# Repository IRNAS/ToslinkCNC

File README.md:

# ToslinkCNC

CNC machine is usually controlled via parallel bus, containing six signals. For each of the three axes there are two signals: STEP and DIR. At each positive edge of the STEP signal, the corresponding stepper motor moves into direction set by DIR signal. In addition to these six signals, there can also be other general purpose control signals.

Parallel bus on longer distances and in noisy environment can be susceptible to electromagnetic interferences. Because of this we decided to design an interface to transport these parallel signals via an optical link. For successful transfer via optical fiber the first thing that must be done is to convert parallel data to serial bit stream. Moreover, because of the inherent design of optical transmitters and receivers, serial data must also be Manchester encoded.

Our design is based on [Serializer / Deserializer for Audio Fiber Optic](http://opencores.org/project,parallel_io_through_fiber) project published on Open Cores. 

## Use cases
ToslinkCNC has been developed for use with [GoodenoughCNC Plasma](http://goodenoughcnc.eu) cutter as our answer to continuous problems with electrical noise and interference. The following configuration is used in the system. 

## Toslink Receiver-transceiver

For each motor on the CNC machine there is one PCB, containing Toslink receiver. Receiver PCB, together with motor driver, can be mounted on the motor. Receiver is being used with [PoLabs' PoStep25-32 stepper motor driver](http://www.poscope.com/PoStep25-32). PCB is being powered through motor driver connector using +5V. To enable this the +5V supply from motor driver should be connected to unused 9th pin on the driver's IDC connector usign a piece of insulated wire. PCB consists of one CPLD, two optical transmitters, one optical receiver, one DIP switch for selecting the axis and one limit switch / trigger connector. Limit switch is insulated through an optocoupler and trigger output is open drain type. Toslink transmitter DLT1111 and Toslink receiver DLR1111 were used, which enable data transfer speed up to 16 Mbps. We used Xilinx XC9572XL CPLD to implement the necessary logic for protocol conversion. Receivers can also be connected in daisy chain.

### Using IDC-10 connector:

### Using terminal blocks:

## Toslink Transmitter

Transmitter consists of two PCBs, an Arduino sield and a Toslink transciever. Both PCBs are stacked together. Toslink transciever PCB is identical to one used for receiver. Arduino shield consists of headers for Arduino and connectors for [CNC USB Controller Mk3/4 from Planet CNC](http://www.planet-cnc.com/index.php?page=hardware) and PoStep25-32 driver. There is also a terminal block for connecting limit switches and trigger signals. Circuit can be powered either through terminal block (+5V), through Arduino Uno if attached as a shield, or from Planet CNC Controller.

## Toslink Transmitter / Arduino Shield

## Toslink Transmitter / Planet CNC

## Toslink Transmitter / Raspberry Pi Shield

## Firmware Description

All data is being transmitted in frames of fixed length. Frames are transmitted without gaps between them. Each frame contains 3 direction values, 3 step values, vaule of enable signal, 3 values of limit/end switch signals (these fields are being shared with 3 trigger values), parity bits and frame delimiter. To detect parity bit corruption, both even and odd parity bits are being transmitted. Transmitter places direction, step, enable and trigger values in new frame, adds calculated parity bits and sends the frame to the first receiver in daisy chain. Receiver reads the enable value and direction, step and trigger values ( based on axis selection). Receiver replaces the correspondig trigger value with limit switch value, calculates new parity bits and sends this new frame to the next receiver in dasy chain. Output of the last receiver in dasy chain is connected to transmitter input. Transmitter reads all three limit switch values from received frame.

Data in optical fiber is manchester encoded. For logic '0', logic '1' and frame delimiter three different patterns are being used. They were selected so that all of them have the same length and are completely different from each other. Decoding is based on time elapsed between two rising edges of clock. If elapsed time is shorter than 12 clock cycles, receiver decodes it as a short step. If it's longer than 12 and shorter than 20 clock cycles, then it's decoded as a medium step. If elapsed time is longer than 20 clock cycles, it's decoded as a long step.

Main transmitter module consists of a step sampler and an optical transmitter. Step sampler samples and shapes incomming step, direction, enable and trigger signals and passes them forward to the optical transmitter. Optical transmitter handles data framing, manchester encoding and sends encoded data to Toslink transmitter.

Block diagram of step sampler is presented in figure below:

Optical transmitter consists of shift register and manchester encoder. Shift register block diagram is presented in figure below:

Manchester encoder consists of three look-up tables and one multiplexer. If value of *tx_output* is "00" the '0' pattern, if  "01" the '1' pattern and if "10" the DEL pattern is generated on the output.

Main receiver module consists of an optical receiver and a step generator. Optical receiver accepts signal from Toslink receiver, decodes it and passes extracted data to step generator. It also adds limit signal values, calculates new parity, manchester encodes data and passes it foward to both Tolsink transmitters. Step generator correctly shapes the received signals.

Optical receiver consists of manchester decoder, shift register and manchester encoder (which is identical to the one used in transmitter). Block diagram of receiver shift register is presented in figure below:

Manchester decoder consists of a simple low-pass filter and a step sampler.

Step sampler is a finite state machine. It's diagram of possible states is presented in figure below. Movement between states is based on received step width: short, medium or long. If step width is too long, the connection is lost and motor driver is disabled (enable signal equals to '1'). As soon as the correct manchester symbol is received, the connection is again established.

## Known Isues

 * There is not enough room on the CPLD to hold both, the transmitter and the receiver. To enable transfer of limit switch signals from receivers back to transmitter, there would also need to be an additional optical receiver implemented on the transmitter PCB's CPLD. This problem can be solved by stacking two transcievers one over another. Firmware for the second transciever is available in [Transmitter](Transmitter/return path receiver CPLD VHDL code) folder.

---

#### License

All our projects are as usefully open-source as possible.

Hardware including documentation is licensed under [CERN OHL v.1.2. license](http://www.ohwr.org/licenses/cern-ohl/v1.2)

Firmware and software originating from the project is licensed under [GNU GENERAL PUBLIC LICENSE v3](http://www.gnu.org/licenses/gpl-3.0.en.html).

Open data generated by our projects is licensed under [CC0](https://creativecommons.org/publicdomain/zero/1.0/legalcode).

All our websites and additional documentation are licensed under [Creative Commons Attribution-ShareAlike 4 .0 Unported License] (https://creativecommons.org/licenses/by-sa/4.0/legalcode).

What this means is that you can use hardware, firmware, software and documentation without paying a royalty and knowing that you'll be able to use your version forever. You are also free to make changes but if you share these changes then you have to do so on the same conditions that you enjoy.

Koruza, GoodEnoughCNC and IRNAS are all names and marks of Institut IRNAS Rače. 
You may use these names and terms only to attribute the appropriate entity as required by the Open Licences referred to above. You may not use them in any other way and in particular you may not use them to imply endorsement or authorization of any hardware that you design, make or sell.

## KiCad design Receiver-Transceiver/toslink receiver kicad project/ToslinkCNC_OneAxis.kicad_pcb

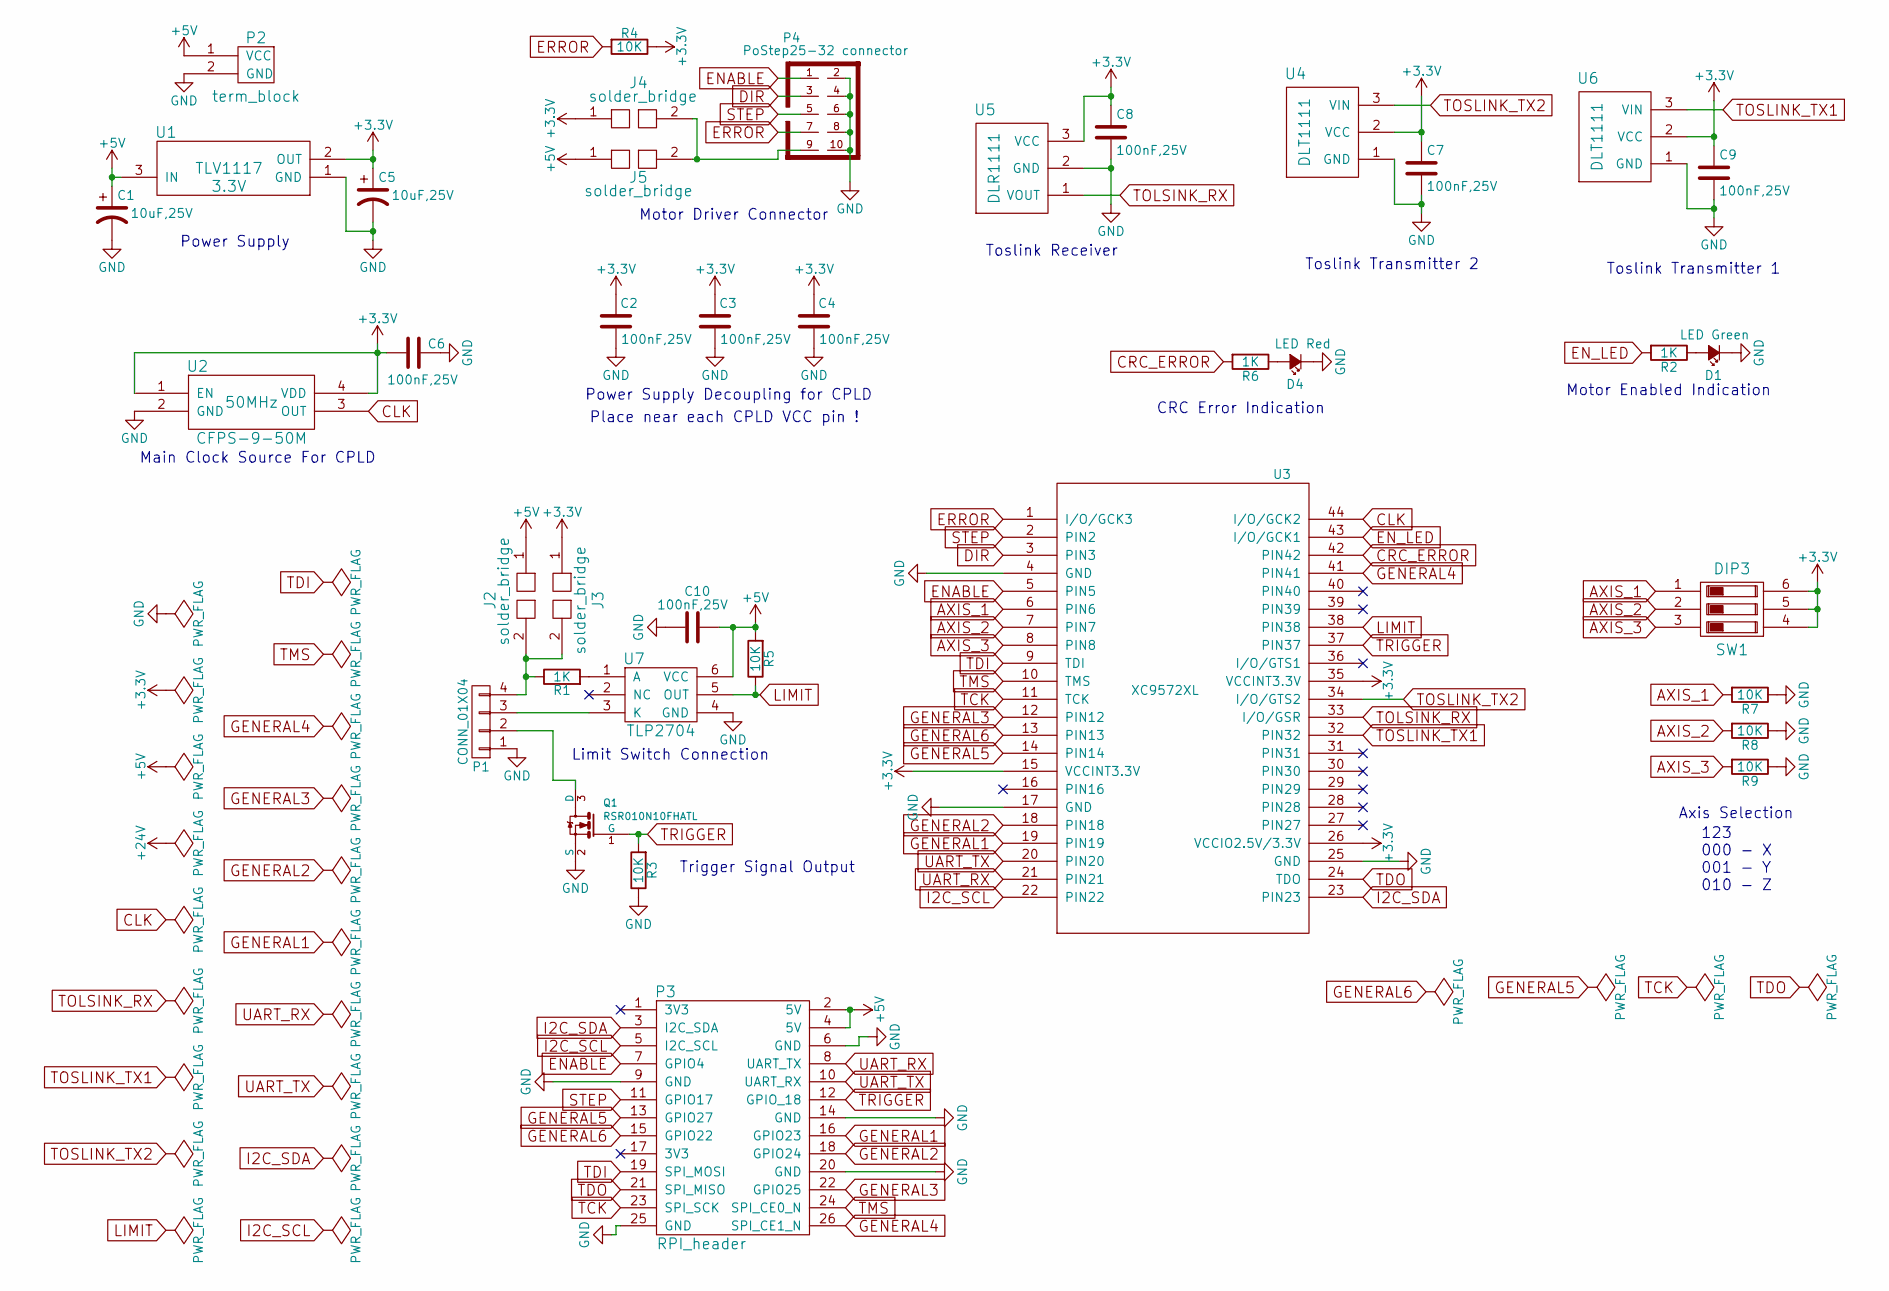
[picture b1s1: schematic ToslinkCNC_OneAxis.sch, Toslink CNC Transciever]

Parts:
C1, C5: 10uF,25V; TantalC_SizeB_EIA-3528_HandSoldering
C2, C3, C4, C6, C7, C8, C9, C10: 100nF,25V; C_0603_HandSoldering
D1: LED Green; LED_0603_HandSoldering
D4: LED Red; LED_0603_HandSoldering
J2, J3, J4, J5: solder_bridge
P1: CONN_01X04; terminal_block_2_5mm_4pole
P2: term_block; terminal_block_2_5mm
P3: RPI_header; Pin_Header_Straight_2x13
P4: PoStep25-32 connector; VASCH5x2
Q1: RSR010N10FHATL; SOT-23
R1, R2, R6: 1K; R_0603_HandSoldering
R3, R4, R5, R7, R8, R9: 10K; R_0603_HandSoldering
SW1: DIP3; OMRON_ELECTRONIC_COMPONENTS_A6S-3102-H_DIP_Switch
U1: TLV1117; SOT-223
U2: CFPS-9-50M
U3: XC9572XL; VQFP44
U4, U6: DLT1111
U5: DLR1111
U7: TLP2704

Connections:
+3V3: C2.2, C3.2, C4.2, C5.1, C6.2, C7.1, C8.1, C9.1, J3.1, J4.1, R4.1, SW1.4, SW1.5, SW1.6, U1.2 (OUT), U2.1 (EN), U2.4 (VDD), U3.15 (VCCINT3.3V), U3.26 (VCCIO2.5V/3.3V), U3.35 (VCCINT3.3V), U4.2 (VCC), U5.3 (VCC), U6.2 (VCC)
+5V: C1.1, C10.1, J2.1, J5.1, P2.1 (VCC), P3.2 (5V), P3.4 (5V), R5.2, U1.3 (IN), U7.6 (VCC)
AXIS_1: R7.2, SW1.1, U3.6 (PIN6)
AXIS_2: R8.2, SW1.2, U3.7 (PIN7)
AXIS_3: R9.2, SW1.3, U3.8 (PIN8)
CLK: U2.3 (OUT), U3.44 (I/O/GCK2)
CRC_ERROR: R6.2, U3.42 (PIN42)
DIR: P4.3, U3.3 (PIN3)
ENABLE: P3.7 (GPIO4), P4.1, U3.5 (PIN5)
EN_LED: R2.2, U3.43 (I/O/GCK1)
ERROR: P4.7, R4.2, U3.1 (I/O/GCK3)
GENERAL1: P3.16 (GPIO23), U3.19 (PIN19)
GENERAL2: P3.18 (GPIO24), U3.18 (PIN18)
GENERAL3: P3.22 (GPIO25), U3.12 (PIN12)
GENERAL4: P3.26 (SPI_CE1_N), U3.41 (PIN41)
GENERAL5: P3.13 (GPIO27), U3.14 (PIN14)
GENERAL6: P3.15 (GPIO22), U3.13 (PIN13)
GND: C1.2, C2.1, C3.1, C4.1, C5.2, C6.1, C7.2, C8.2, C9.2, C10.2, D1.1 (K), D4.1 (K), P1.1, P2.2 (GND), P3.6 (GND), P3.9 (GND), P3.14 (GND), P3.20 (GND), P3.25 (GND), P4.2, P4.4, P4.6, P4.8, P4.10, Q1.2 (S), R3.1, R7.1, R8.1, R9.1, U1.1 (GND), U2.2 (GND), U3.4 (GND), U3.17 (GND), U3.25 (GND), U4.1 (GND), U5.2 (GND), U6.1 (GND), U7.4 (GND)
I2C_SCL: P3.5 (I2C_SCL), U3.22 (PIN22)
I2C_SDA: P3.3 (I2C_SDA), U3.23 (PIN23)
LIMIT: R5.1, U3.38 (PIN38), U7.5 (OUT)
unnamed: D1.2 (A), R2.1
unnamed: D4.2 (A), R6.1
unnamed: J2.2, J3.2, P1.4, R1.1
unnamed: J4.2, J5.2, P4.9
unnamed: P1.2, Q1.3 (D)
unnamed: P1.3, U7.3 (K)
unnamed: R1.2, U7.1 (A)
STEP: P3.11 (GPIO17), P4.5, U3.2 (PIN2)
TCK: P3.23 (SPI_SCK), U3.11 (TCK)
TDI: P3.19 (SPI_MOSI), U3.9 (TDI)
TDO: P3.21 (SPI_MISO), U3.24 (TDO)
TMS: P3.24 (SPI_CE0_N), U3.10 (TMS)
TOLSINK_RX: U3.33 (I/O/GSR), U5.1 (VOUT)
TOSLINK_TX1: U3.32 (PIN32), U6.3 (VIN)
TOSLINK_TX2: U3.34 (I/O/GTS2), U4.3 (VIN)
TRIGGER: P3.12 (GPIO_18), Q1.1 (G), R3.2, U3.37 (PIN37)
UART_RX: P3.8 (UART_TX), U3.21 (PIN21)
UART_TX: P3.10 (UART_RX), U3.20 (PIN20)

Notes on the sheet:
Power Supply Decoupling for CPLD
Axis Selection
Motor Enabled Indication
CRC Error Indication
Place near each CPLD VCC pin !
Main Clock Source For CPLD
Motor Driver Connector
Toslink Transmitter 2
Toslink Receiver
Toslink Transmitter 1
Limit Switch Connection
Power Supply
123 000 - X 001 - Y 010 - Z
Trigger Signal Output

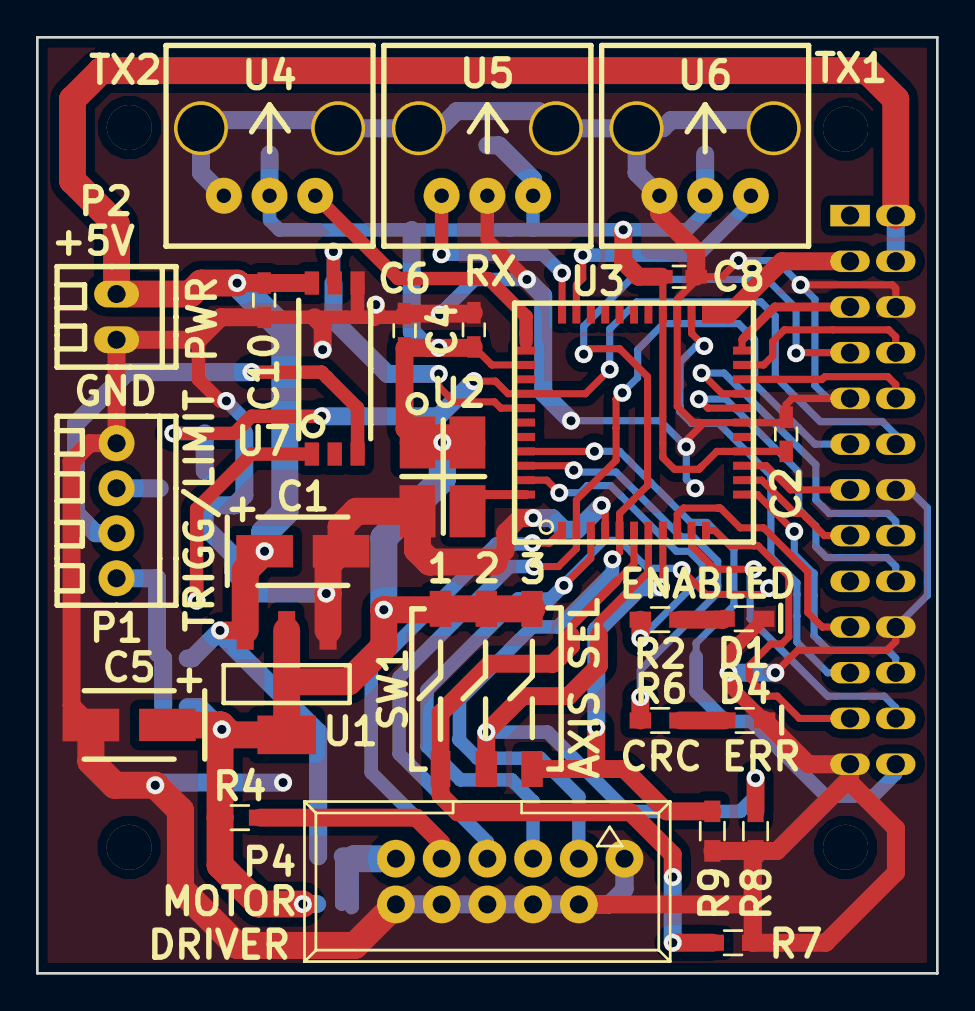
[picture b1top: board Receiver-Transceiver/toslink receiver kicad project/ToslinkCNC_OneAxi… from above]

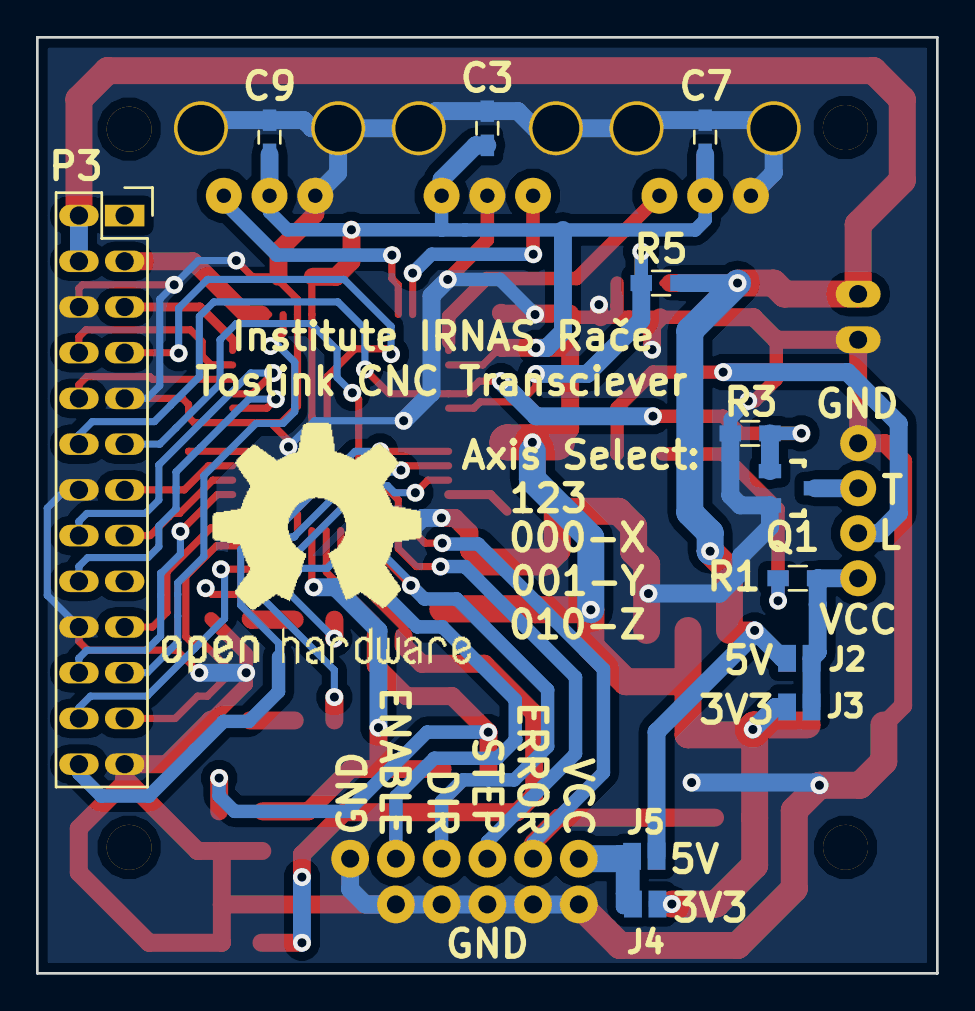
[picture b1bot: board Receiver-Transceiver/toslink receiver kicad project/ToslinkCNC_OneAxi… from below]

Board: 2 copper layers, 50.0 x 52.0 mm, 38 parts (11 on the bottom side), 39 nets.

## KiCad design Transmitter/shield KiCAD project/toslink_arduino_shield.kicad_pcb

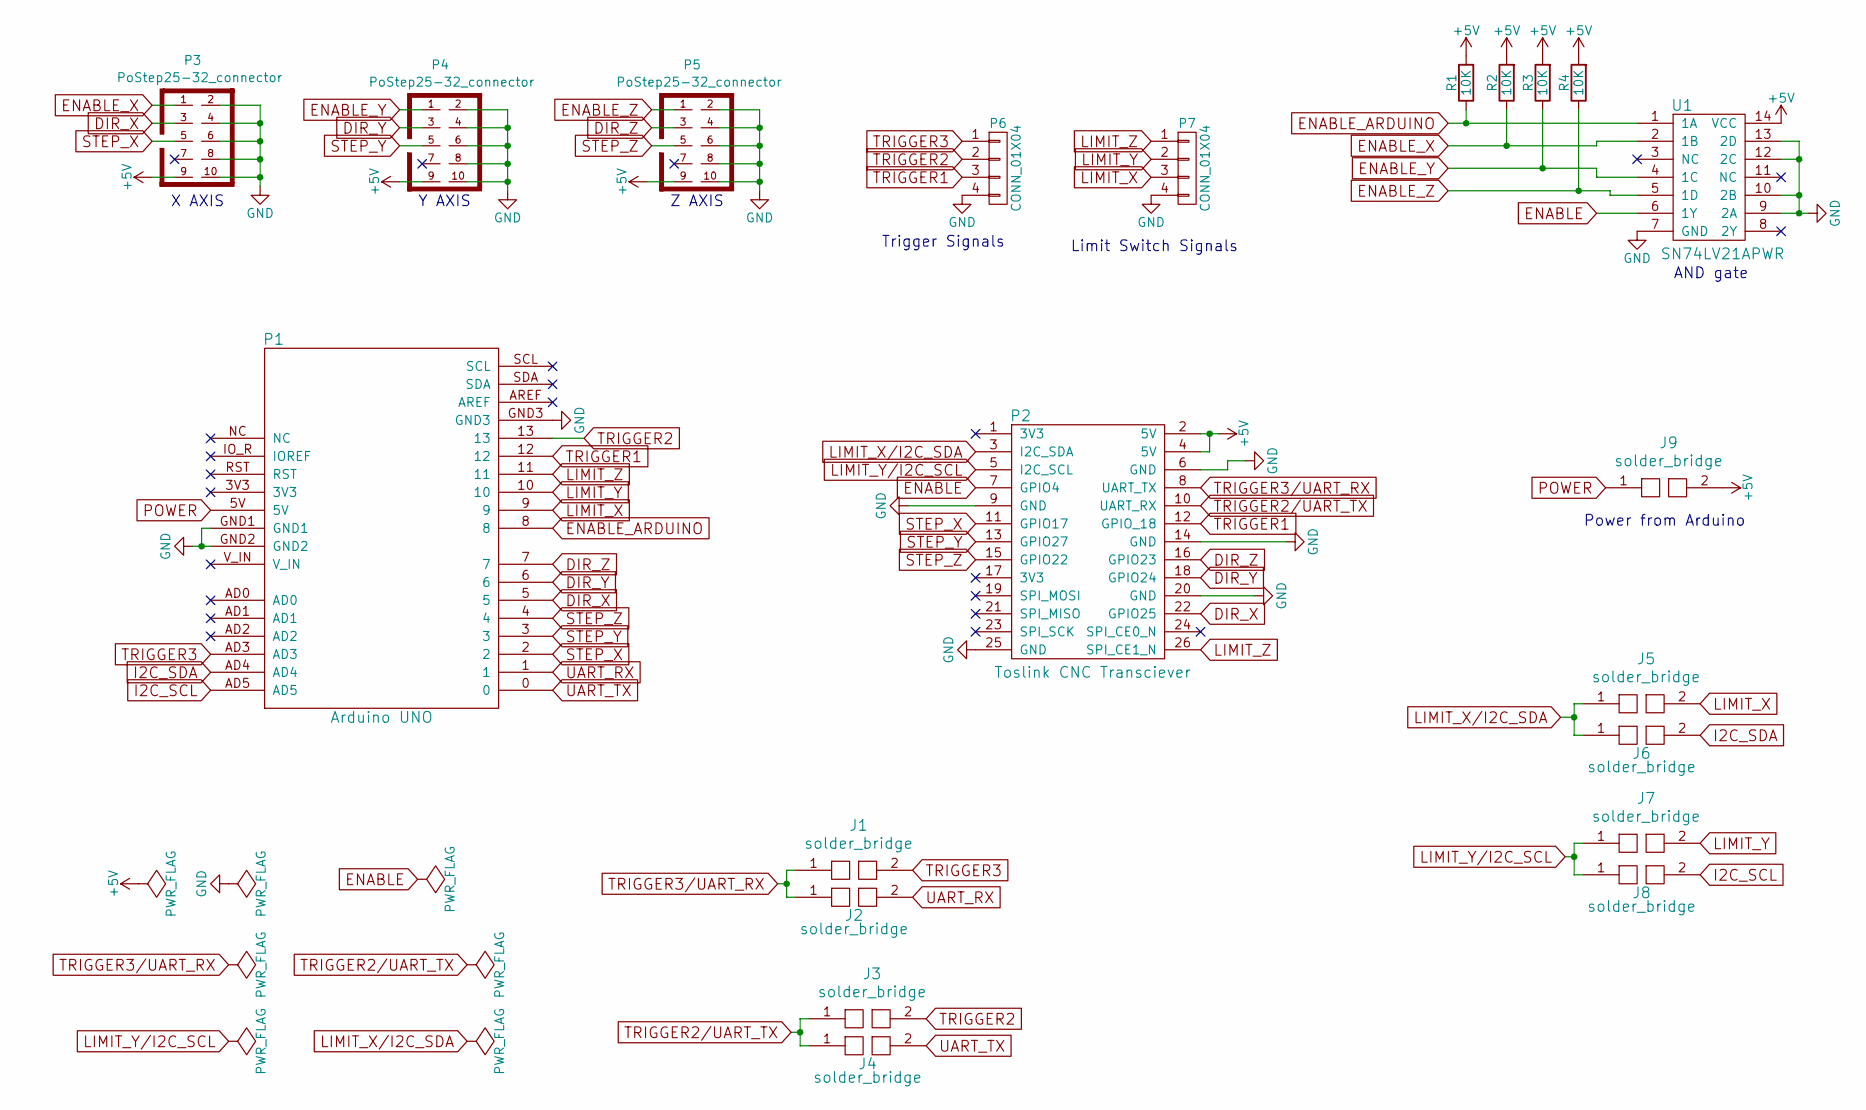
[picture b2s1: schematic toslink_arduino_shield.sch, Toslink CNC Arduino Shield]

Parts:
J1, J2, J3, J4, J5, J6, J7, J8, J9: solder_bridge
P1: Arduino UNO; ARDUINO_SHIELD
P2: Toslink CNC Transciever; toslink_pcb
P3, P4, P5: PoStep25-32_connector; VASCH5x2
P6, P7: CONN_01X04; terminal_block_2_5mm_4pole
R1, R2, R3, R4: 10K; R_0603_HandSoldering
U1: SN74LV21APWR; SN74LV21APWR_ANDGate_tssop14

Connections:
+5V: J9.2, P2.2 (5V), P2.4 (5V), P3.9, P4.9, P5.9, R1.2, R2.2, R3.2, R4.2, U1.14 (VCC)
DIR_X: P1.5, P2.22 (GPIO25), P3.3
DIR_Y: P1.6, P2.18 (GPIO24), P4.3
DIR_Z: P1.7, P2.16 (GPIO23), P5.3
ENABLE: P2.7 (GPIO4), U1.6 (1Y)
ENABLE_ARDUINO: P1.8, R1.1, U1.1 (1A)
ENABLE_X: P3.1, R2.1, U1.2 (1B)
ENABLE_Y: P4.1, R3.1, U1.4 (1C)
ENABLE_Z: P5.1, R4.1, U1.5 (1D)
GND: P1.GND1, P1.GND2, P1.GND3, P2.6 (GND), P2.9 (GND), P2.14 (GND), P2.20 (GND), P2.25 (GND), P3.2, P3.4, P3.6, P3.8, P3.10, P4.2, P4.4, P4.6, P4.8, P4.10, P5.2, P5.4, P5.6, P5.8, P5.10, P6.4, P7.4, U1.7 (GND), U1.9 (2A), U1.10 (2B), U1.12 (2C), U1.13 (2D)
I2C_SCL: J8.2, P1.AD5
I2C_SDA: J6.2, P1.AD4
LIMIT_X: J5.2, P1.9, P7.3
LIMIT_X/I2C_SDA: J5.1, J6.1, P2.3 (I2C_SDA)
LIMIT_Y: J7.2, P1.10, P7.2
LIMIT_Y/I2C_SCL: J7.1, J8.1, P2.5 (I2C_SCL)
LIMIT_Z: P1.11, P2.26 (SPI_CE1_N), P7.1
POWER: J9.1, P1.5V
STEP_X: P1.2, P2.11 (GPIO17), P3.5
STEP_Y: P1.3, P2.13 (GPIO27), P4.5
STEP_Z: P1.4, P2.15 (GPIO22), P5.5
TRIGGER1: P1.12, P2.12 (GPIO_18), P6.3
TRIGGER2: J3.2, P1.13, P6.2
TRIGGER2/UART_TX: J3.1, J4.1, P2.10 (UART_RX)
TRIGGER3: J1.2, P1.AD3, P6.1
TRIGGER3/UART_RX: J1.1, J2.1, P2.8 (UART_TX)
UART_RX: J2.2, P1.1
UART_TX: J4.2, P1.0

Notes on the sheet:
X AXIS
Y AXIS
Z AXIS
Limit Switch Signals
Trigger Signals
Power from Arduino
AND gate

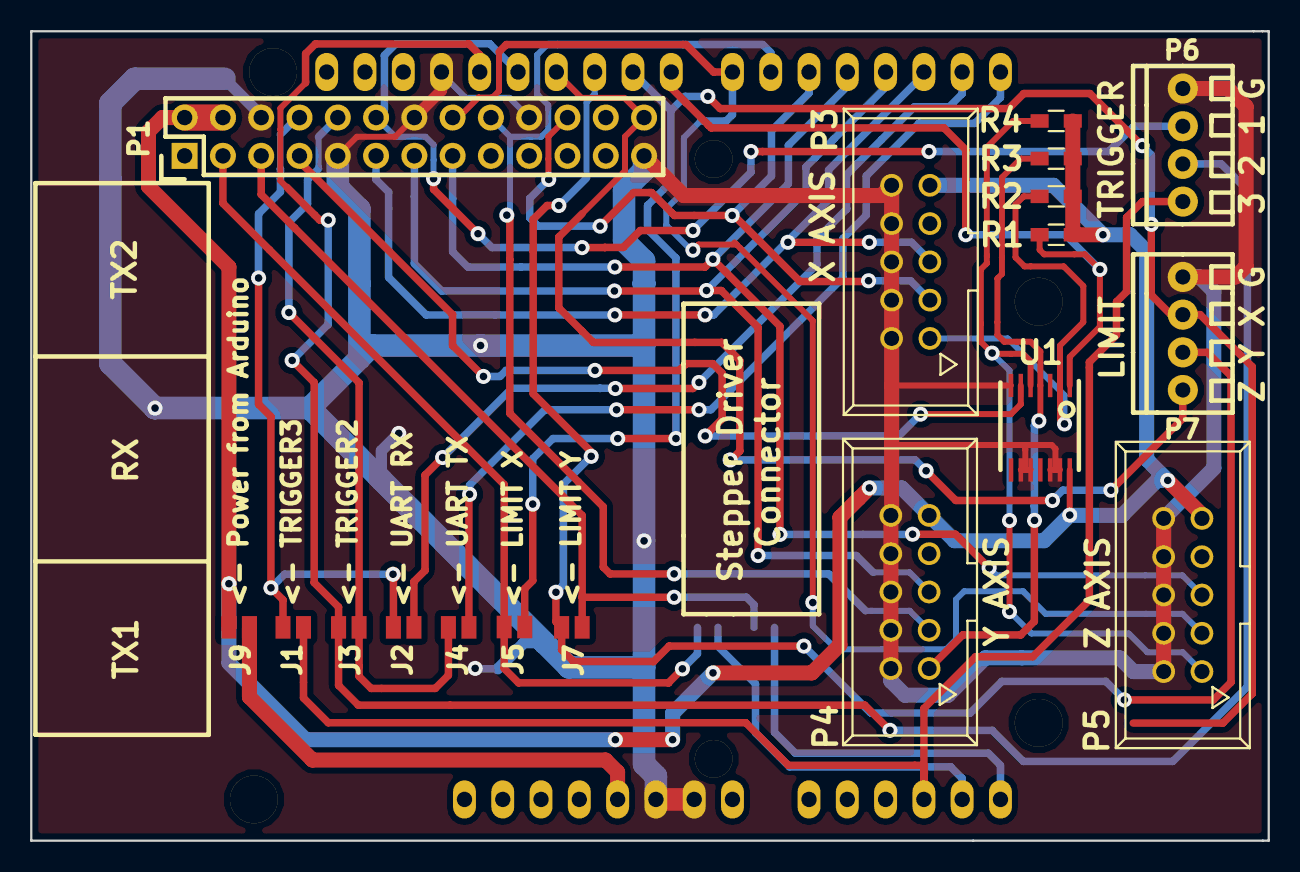
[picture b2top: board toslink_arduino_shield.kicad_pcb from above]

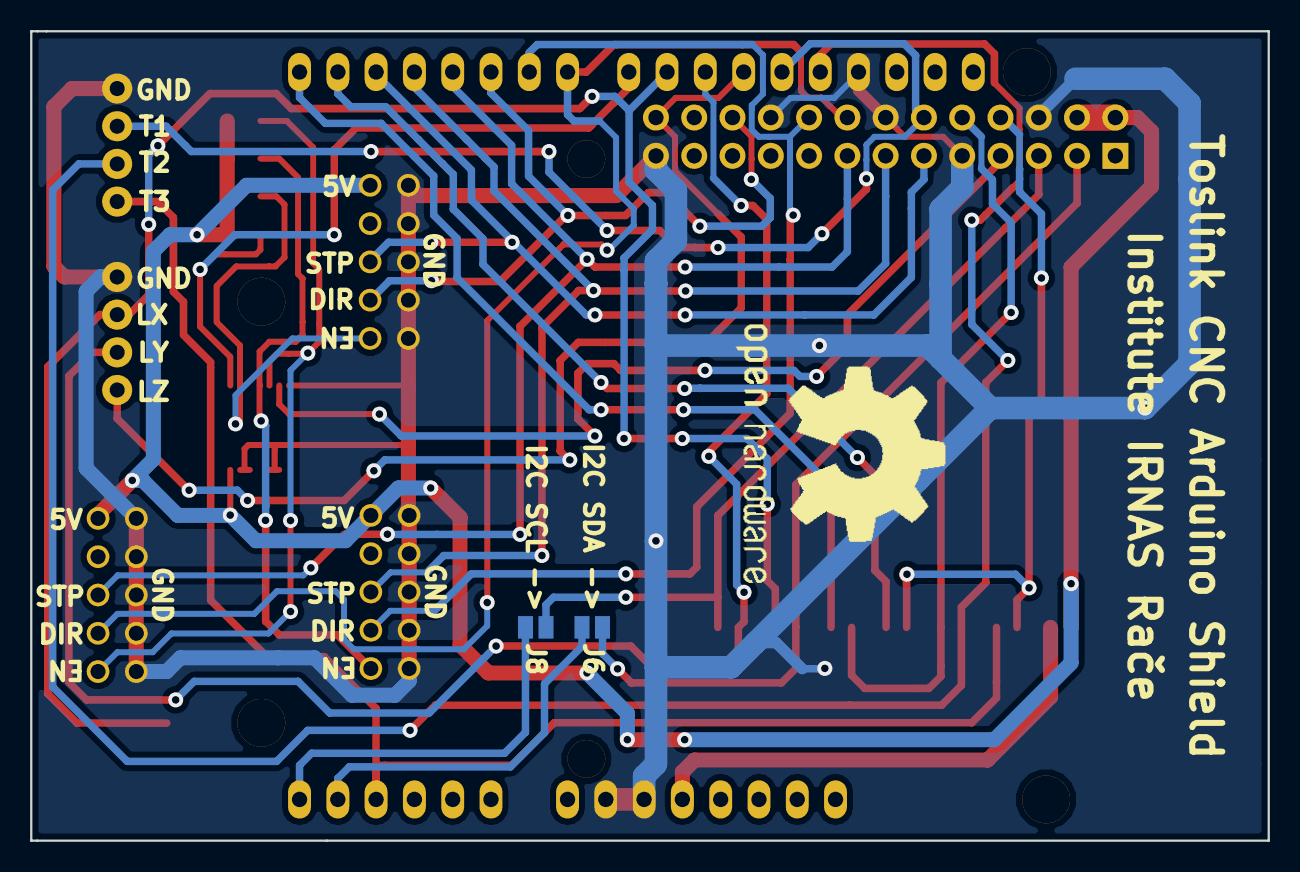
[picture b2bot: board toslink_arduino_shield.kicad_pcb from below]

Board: 2 copper layers, 82.1 x 53.7 mm, 21 parts (2 on the bottom side), 28 nets.

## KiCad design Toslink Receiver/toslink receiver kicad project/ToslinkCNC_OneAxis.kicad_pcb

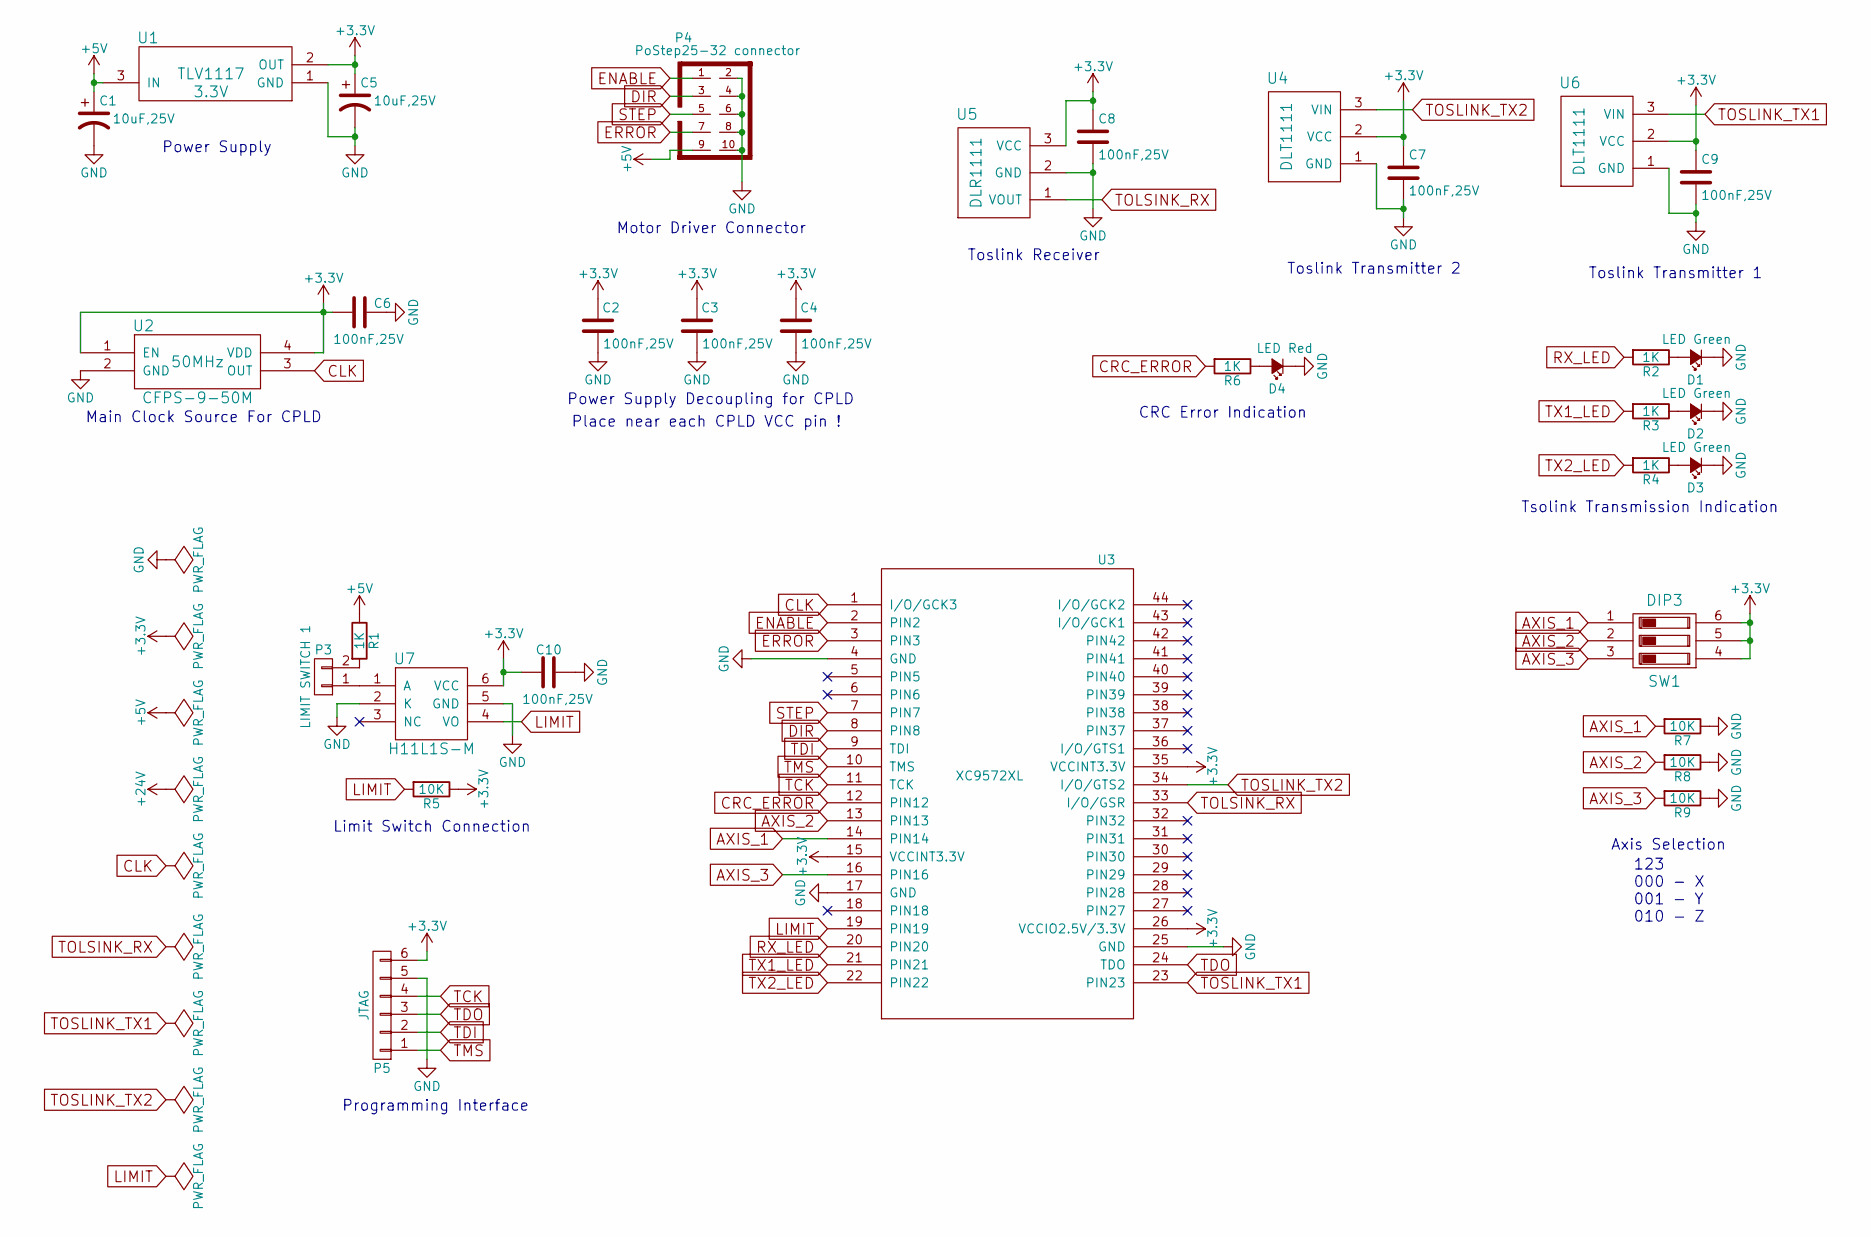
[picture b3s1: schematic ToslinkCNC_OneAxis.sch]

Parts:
C1, C5: 10uF,25V; TantalC_SizeB_EIA-3528_HandSoldering
C2, C3, C4, C6, C7, C8, C9, C10: 100nF,25V; C_0603_HandSoldering
D1, D2, D3: LED Green; LED_0603_HandSoldering
D4: LED Red; LED_0603_HandSoldering
P3: LIMIT SWITCH 1; Socket_Strip_Straight_1x02
P4: PoStep25-32 connector; VASCH5x2
P5: JTAG; Socket_Strip_Straight_1x06
R1, R2, R3, R4, R6: 1K; R_0603_HandSoldering
R5, R7, R8, R9: 10K; R_0603_HandSoldering
SW1: DIP3; OMRON_ELECTRONIC_COMPONENTS_A6S-3102-H_DIP_Switch
U1: TLV1117; SOT-223
U2: CFPS-9-50M
U3: XC9572XL; VQFP44
U4, U6: DLT1111
U5: DLR1111
U7: H11L1S-M

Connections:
+3V3: C2.2, C3.2, C4.2, C5.1, C6.2, C7.1, C8.1, C9.1, C10.2, P5.6, R5.1, SW1.4, SW1.5, SW1.6, U1.2 (OUT), U2.1 (EN), U2.4 (VDD), U3.15 (VCCINT3.3V), U3.26 (VCCIO2.5V/3.3V), U3.35 (VCCINT3.3V), U4.2 (VCC), U5.3 (VCC), U6.2 (VCC), U7.6 (VCC)
+5V: C1.1, P4.9, R1.1, U1.3 (IN)
AXIS_X: R7.2, SW1.1, U3.14 (PIN14)
AXIS_Y: R8.2, SW1.2, U3.13 (PIN13)
AXIS_Z: R9.2, SW1.3, U3.16 (PIN16)
CLK: U2.3 (OUT), U3.1 (I/O/GCK3)
CRC_ERROR: R6.2, U3.12 (PIN12)
DIR: P4.3, U3.8 (PIN8)
ENABLE: P4.1, U3.2 (PIN2)
ERROR: P4.7, U3.3 (PIN3)
GND: C1.2, C2.1, C3.1, C4.1, C5.2, C6.1, C7.2, C8.2, C9.2, C10.1, D1.1 (K), D2.1 (K), D3.1 (K), D4.1 (K), P4.2, P4.4, P4.6, P4.8, P4.10, P5.5, R7.1, R8.1, R9.1, U1.1 (GND), U2.2 (GND), U3.4 (GND), U3.17 (GND), U3.25 (GND), U4.1 (GND), U5.2 (GND), U6.1 (GND), U7.2 (K), U7.5 (GND)
LIMIT: R5.2, U3.19 (PIN19), U7.4 (VO)
unnamed: D1.2 (A), R2.1
unnamed: D2.2 (A), R3.1
unnamed: D3.2 (A), R4.1
unnamed: D4.2 (A), R6.1
unnamed: P3.1, U7.1 (A)
unnamed: P3.2, R1.2
RX_LED: R2.2, U3.20 (PIN20)
STEP: P4.5, U3.7 (PIN7)
TCK: P5.4, U3.11 (TCK)
TDI: P5.2, U3.9 (TDI)
TDO: P5.3, U3.24 (TDO)
TMS: P5.1, U3.10 (TMS)
TOLSINK_RX: U3.33 (I/O/GSR), U5.1 (VOUT)
TOSLINK_TX1: U3.23 (PIN23), U6.3 (VIN)
TOSLINK_TX2: U3.34 (I/O/GTS2), U4.3 (VIN)
TX1_LED: R3.2, U3.21 (PIN21)
TX2_LED: R4.2, U3.22 (PIN22)

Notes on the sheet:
Power Supply Decoupling for CPLD
Axis Selection
Tsolink Transmission Indication
CRC Error Indication
Place near each CPLD VCC pin !
Programming Interface
Main Clock Source For CPLD
Motor Driver Connector
Toslink Transmitter 2
Toslink Receiver
Toslink Transmitter 1
Limit Switch Connection
Power Supply
123 000 - X 001 - Y 010 - Z

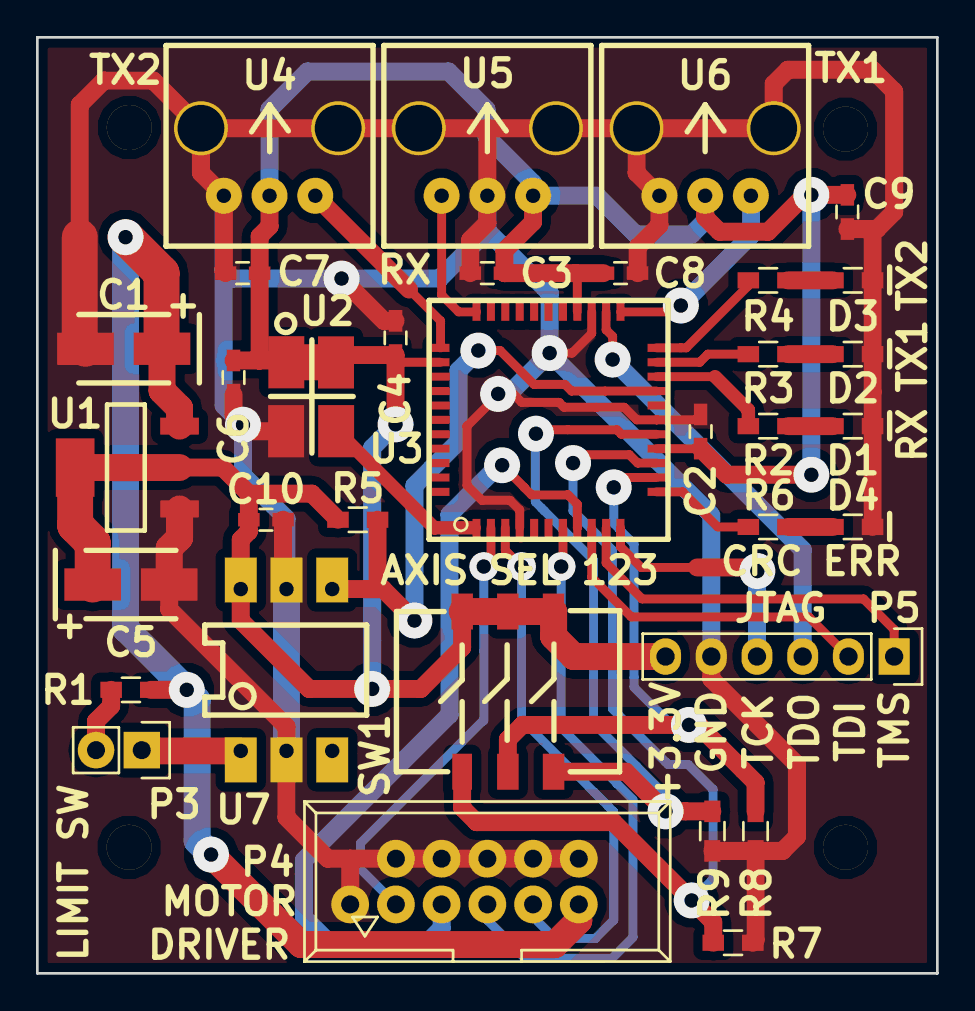
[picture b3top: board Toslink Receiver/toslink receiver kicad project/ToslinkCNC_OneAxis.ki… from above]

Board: 2 copper layers, 50.0 x 52.0 mm, 34 parts (0 on the bottom side), 29 nets.

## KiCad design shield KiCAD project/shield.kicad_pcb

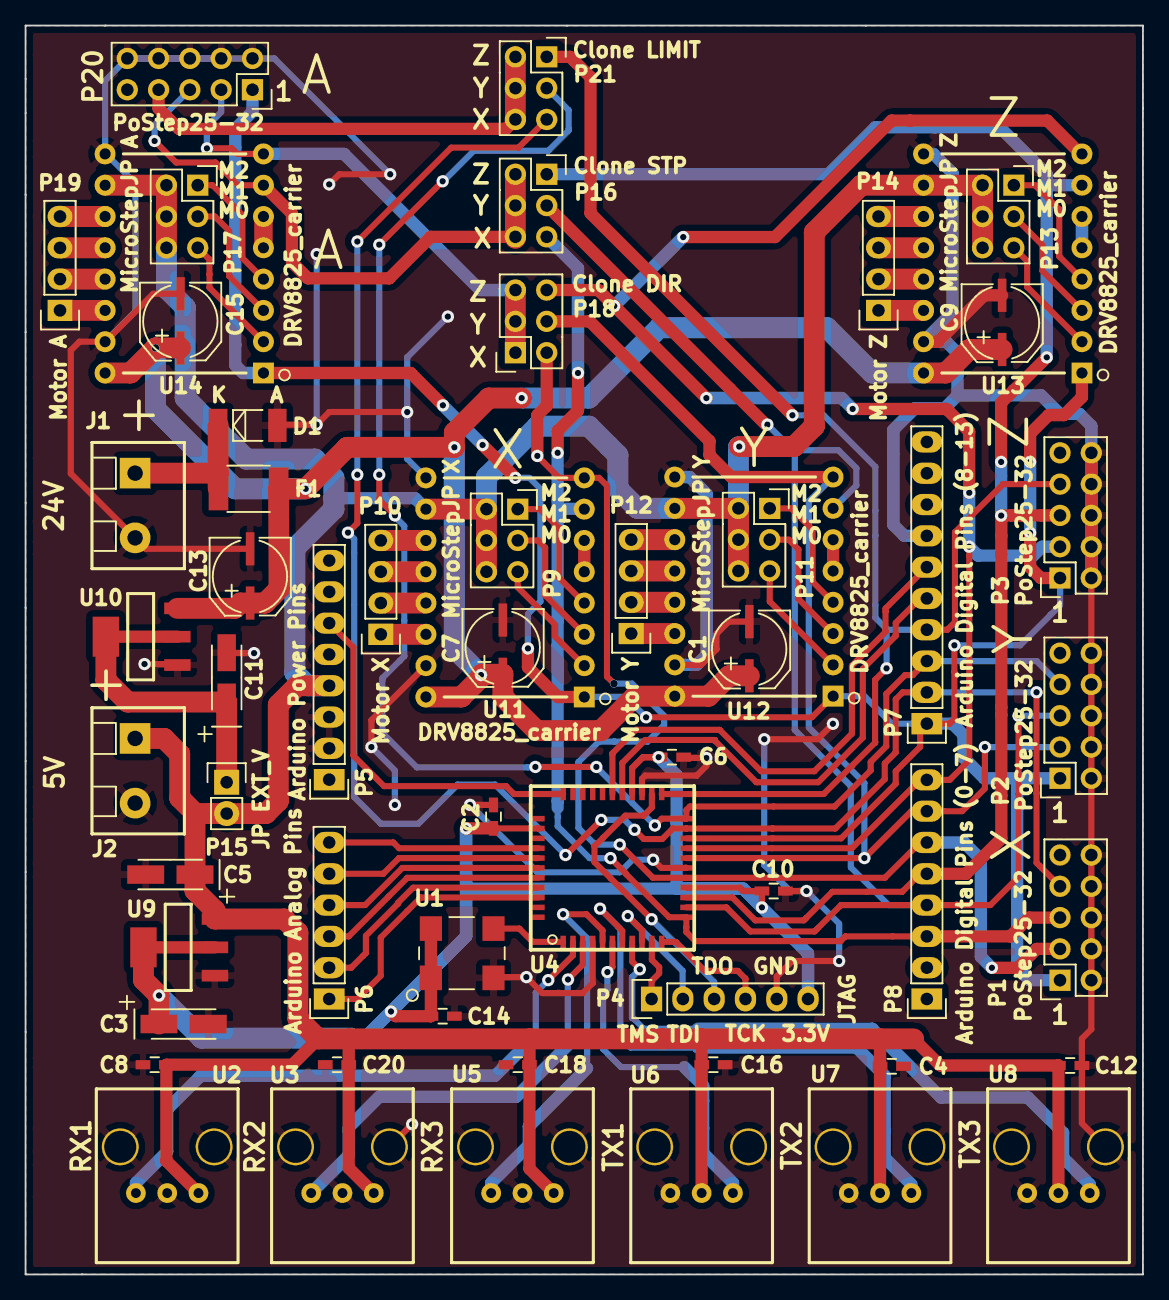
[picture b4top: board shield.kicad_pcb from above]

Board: 2 copper layers, 90.7 x 101.3 mm, 57 parts (0 on the bottom side), 71 nets.

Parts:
C1, C7, C9, C13, C15: 100uF; smd_can_electrolytic_capacitor
C2, C4, C6, C8, C10, C12, C14, C16, C18, C20: 0,1uF; C_0603_HandSoldering
C3, C5, C11: 10uF; TantalC_SizeA_EIA-3216_HandSoldering
D1: ZENER 24V; MELF_Standard
F1: FUSE; R_1812
J1, J2: term_block; terminal_block
P1, P2, P3, P20: PoStep25-32; Socket_Strip_Straight_2x05
P4: JTAG; Socket_Strip_Straight_1x06
P5: Arduino Power Pins; Socket_Strip_Straight_1x08
P6: Arduino Analog Pins; Socket_Strip_Straight_1x06
P7: Arduino Digital Pins (8-13); Socket_Strip_Straight_1x10
P8: Arduino Digital Pins (0-7); Socket_Strip_Straight_1x08
P9: MicroStepJP X; Socket_Strip_Straight_2x03
P10: Motor X; Socket_Strip_Straight_1x04
P11: MicroStepJP Y; Socket_Strip_Straight_2x03
P12: Motor Y; Socket_Strip_Straight_1x04
P13: MicroStepJP Z; Socket_Strip_Straight_2x03
P14: Motor Z; Socket_Strip_Straight_1x04
P15: JP EXT_V; Socket_Strip_Straight_1x02
P16: Clone STP; Socket_Strip_Straight_2x03
P17: MicroStepJP A; Socket_Strip_Straight_2x03
P18: Clone DIR; Socket_Strip_Straight_2x03
P19: Motor A; Socket_Strip_Straight_1x04
P21: Clone LIMIT; Socket_Strip_Straight_2x03
U1: ASV_XO_50MHZ; ASV_XO
U2, U3, U5: DLR1111
U4: XC9572XL; VQFP44
U6, U7, U8: DLT1111
U9, U10: TLV1117; SOT-223
U11, U12, U13, U14: DRV8825_carrier

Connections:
3.3V: C2.1, C3.1, C6.1, C10.1, C14.1, P4.6, U1.1, U1.4, U4.15, U4.26, U4.35, U9.2
5V: C4.1, C5.1, C8.1, C12.1, C16.1, C18.1, C20.1, J2.1, P5.4, P9.2, P9.4, P9.6, P11.2, P11.4, P11.6, P13.2, P13.4, P13.6, P15.2, P17.2, P17.4, P17.6, U2.3, U3.3, U5.3, U6.2, U7.2, U8.2, U9.3, U11.10, U12.10, U13.10, U14.10
A0: P6.1, U4.42
A1: P6.2, U4.41
A2: P6.3, U4.40
A3: P6.4, U4.39
A4: P6.5, U4.38
A5: P6.6, U4.37
CLK: U1.3, U4.1
D2: P1.5, P8.3, P16.5, U4.12, U11.7
D3: P2.5, P8.4, P16.3, U4.13, U12.7
D4: P3.5, P8.5, P16.1, U4.14, U13.7
D5: P1.3, P8.6, P18.2, U4.16, U11.8
D6: P2.3, P8.7, P18.4, U4.18, U12.8
D7: P3.3, P8.8, P18.6, U4.19, U13.8
D8: P1.1, P2.1, P3.1, P7.1, P20.1, U4.20, U11.1, U12.1, U13.1, U14.1
D9: P1.7, P7.2, P21.5, U4.21
D10: P2.7, P7.3, P21.3, U4.22
D11: P3.7, P7.4, P21.1, U4.23
D12: P7.5, U4.27
D13: P7.6, U4.28
DIR_A: P18.1, P18.3, P18.5, P20.3, U14.8
EXT_V: C1.1, C7.1, C9.1, C13.1, C15.1, F1.1, U10.3, U11.16, U12.16, U13.16, U14.16
FIBER_RX1: U2.1, U4.2
FIBER_RX2: U3.1, U4.3
FIBER_RX3: U4.5, U5.1
FIBER_TX1: U4.6, U6.3
FIBER_TX2: U4.7, U7.3
FIBER_TX3: U4.8, U8.3
GND: C1.2, C2.2, C3.2, C4.2, C5.2, C6.2, C7.2, C8.2, C9.2, C10.2, C11.2, C12.2, C13.2, C14.2, C15.2, C16.2, C18.2, C20.2, D1.2, J1.2, J2.2, P1.2, P1.4, P1.6, P1.8, P1.10, P2.2, P2.4, P2.6, P2.8, P2.10, P3.2, P3.4, P3.6, P3.8, P3.10, P4.5, P5.2, P5.3, P7.7, P20.2, P20.4, P20.6, P20.8, P20.10, U1.2, U2.2, U3.2, U4.4, U4.17, U4.25, U5.2, U6.1, U7.1, U8.1, U9.1, U10.1, U11.9, U11.15, U12.9, U12.15, U13.9, U13.15, U14.9, U14.15
LIMIT_A: P20.7, P21.2, P21.4, P21.6
unnamed: C11.1, P15.1, U10.2
unnamed: P9.1, U11.4
unnamed: P9.3, U11.3
unnamed: P9.5, U11.2
unnamed: P10.1, U11.14
unnamed: P10.2, U11.13
unnamed: P10.3, U11.12
unnamed: P10.4, U11.11
unnamed: P11.1, U12.4
unnamed: P11.3, U12.3
unnamed: P11.5, U12.2
unnamed: P12.1, U12.14
unnamed: P12.2, U12.13
unnamed: P12.3, U12.12
unnamed: P12.4, U12.11
unnamed: P13.1, U13.4
unnamed: P13.3, U13.3
unnamed: P13.5, U13.2
unnamed: P14.1, U13.14
unnamed: P14.2, U13.13
unnamed: P14.3, U13.12
unnamed: P14.4, U13.11
unnamed: P17.1, U14.4
unnamed: P17.3, U14.3
unnamed: P17.5, U14.2
unnamed: P19.1, U14.14
unnamed: P19.2, U14.13
unnamed: P19.3, U14.12
unnamed: P19.4, U14.11
unnamed: U11.5, U11.6
unnamed: U12.5, U12.6
unnamed: U13.5, U13.6
unnamed: U14.5, U14.6
POWER: D1.1, F1.2, J1.1
RESET: P5.6, U4.33
STP_A: P16.2, P16.4, P16.6, P20.5, U14.7
TCK: P4.4, U4.11
TDI: P4.2, U4.9
TDO: P4.3, U4.24
TMS: P4.1, U4.10

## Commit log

2015-12-04 Added know isues report.
2016-01-06 Update LICENSE
2016-03-02 Toslink Transmitter Update
2016-03-02 Added files via upload
2016-03-10 Releasing the system
2016-05-09 Update Known Issues
2016-05-13 new images upload
2016-05-13 images update
2016-05-13 images upload
2016-05-13 img size update
2016-05-13 img update
2016-09-07 Minor changes to return path receiver CPLD code
2016-10-21 Added Toslink CNC To PlanetCNC ECO Shield
2016-10-21 Added Planet CNC ECO Shield BOM
